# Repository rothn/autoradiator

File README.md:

# autoradiator
Design and software to control an old-fashioned radiator with a dial. Should work for most old-fashioned installations that are incompatible with consumer IoT stuff.

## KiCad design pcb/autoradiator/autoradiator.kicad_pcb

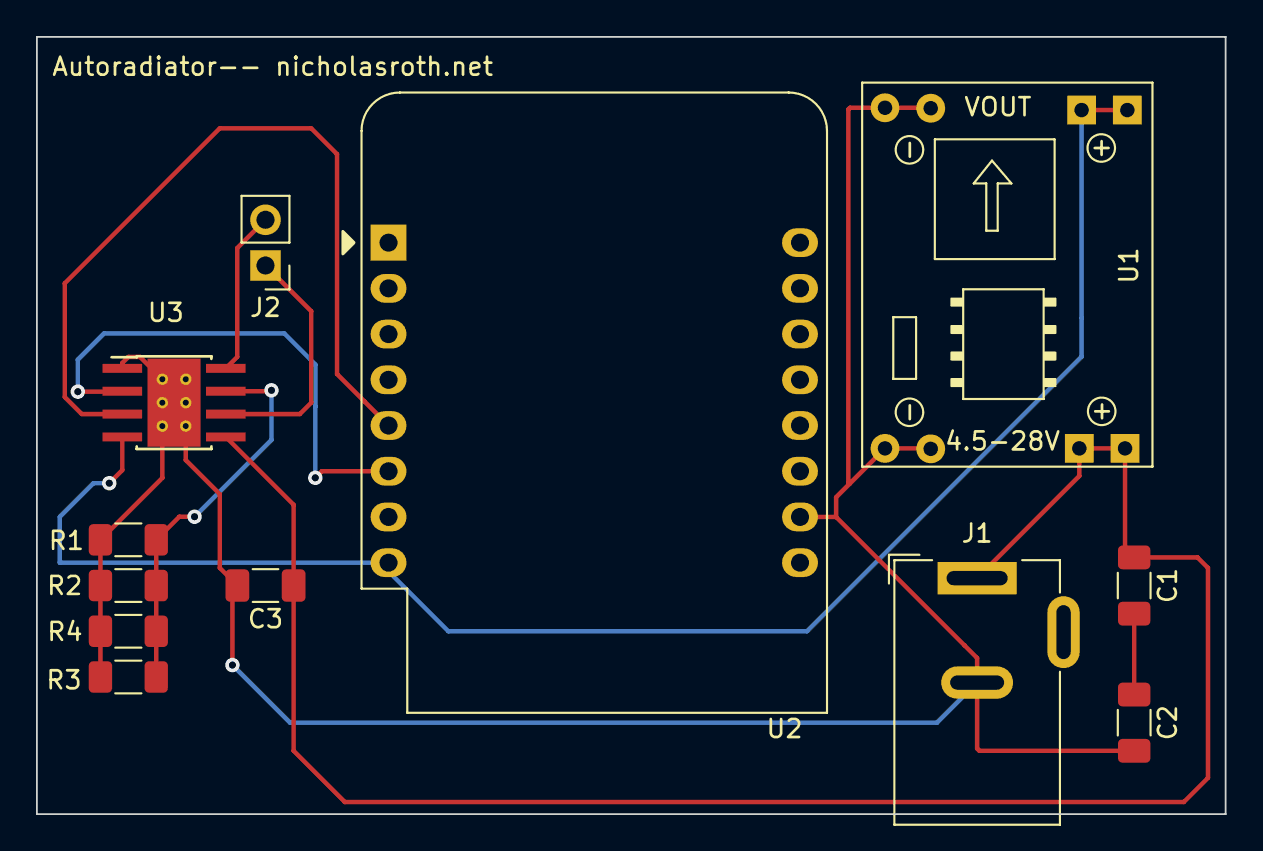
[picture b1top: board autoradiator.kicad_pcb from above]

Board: 2 copper layers, 66.0 x 43.2 mm, 12 parts (0 on the bottom side), 9 nets.

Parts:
C1, C2: 856C; C_1206_3216Metric_Pad1.33x1.80mm_HandSolder
C3: 104C; C_1206_3216Metric_Pad1.33x1.80mm_HandSolder
J1: Barrel Jack; BarrelJack_Wuerth_6941xx301002
J2: Motor Hdr; PinHeader_1x02_P2.54mm_Vertical
R1, R2, R3, R4: 1R; R_1206_3216Metric_Pad1.30x1.75mm_HandSolder
U1: ChineseDCDCBoard; SRT_MPT1584EN_Module
U2: WeMos_D1_mini; WEMOS_D1_mini_light
U3: DRV8870DDA; Texas_HTSOP-8-1EP_3.9x4.9mm_P1.27mm_EP2.95x4.9mm_Mask2.4x3.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

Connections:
+3V3: U1.3 (OUT), U2.8 (3V3), U3.4 (VREF)
+12V: C1.1, C3.1, J1.1, U1.1 (IN), U3.5 (VM)
GND: C2.2, C3.2, J1.2, R1.2, R2.2, R3.2, R4.2, U1.2 (GND), U1.4 (GND), U2.10 (GND), U3.1 (GND), U3.9 (GND)
unnamed: C1.2, C2.1
unnamed: R1.1, R2.1, R3.1, R4.1, U3.7 (ISEN)
unnamed: U2.5 (MISO/D6), U3.3 (IN1)
unnamed: U2.6 (MOSI/D7), U3.2 (IN2)
unnamed: J2.1, U3.6 (OUT1)
unnamed: J2.2, U3.8 (OUT2)

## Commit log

2024-01-20 Add ESPHome config files for radiator controller
2024-01-20 Fix gitignore to prevent publishing secrets
2024-01-21 Add initial PCB design
2024-02-03 Added radiator as heater climate-control device
2024-02-10 Adjusted resistor values to limit current properly for test hardware and updated configuration to use more appropriate controls in homeassistant
2024-02-10 Added schematic for mounting hardware
2024-02-10 Updated PCB to mark some resistors as not populated
2024-02-11 Updated gitignore
2024-10-19 Specify max temperature
2024-10-19 Commit final iteration of v1 mounting design
2024-10-20 Added 3D CAD model of radiator enclosure
2024-10-20 Remove residual file from bad merge
